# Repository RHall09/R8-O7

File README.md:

R8-O7

A repository containing source code for running an autonomous crowd interaction robot.

See https://rhall09.github.io/R8-O7/html/index.html#sec_intro for documentation and inspirations.

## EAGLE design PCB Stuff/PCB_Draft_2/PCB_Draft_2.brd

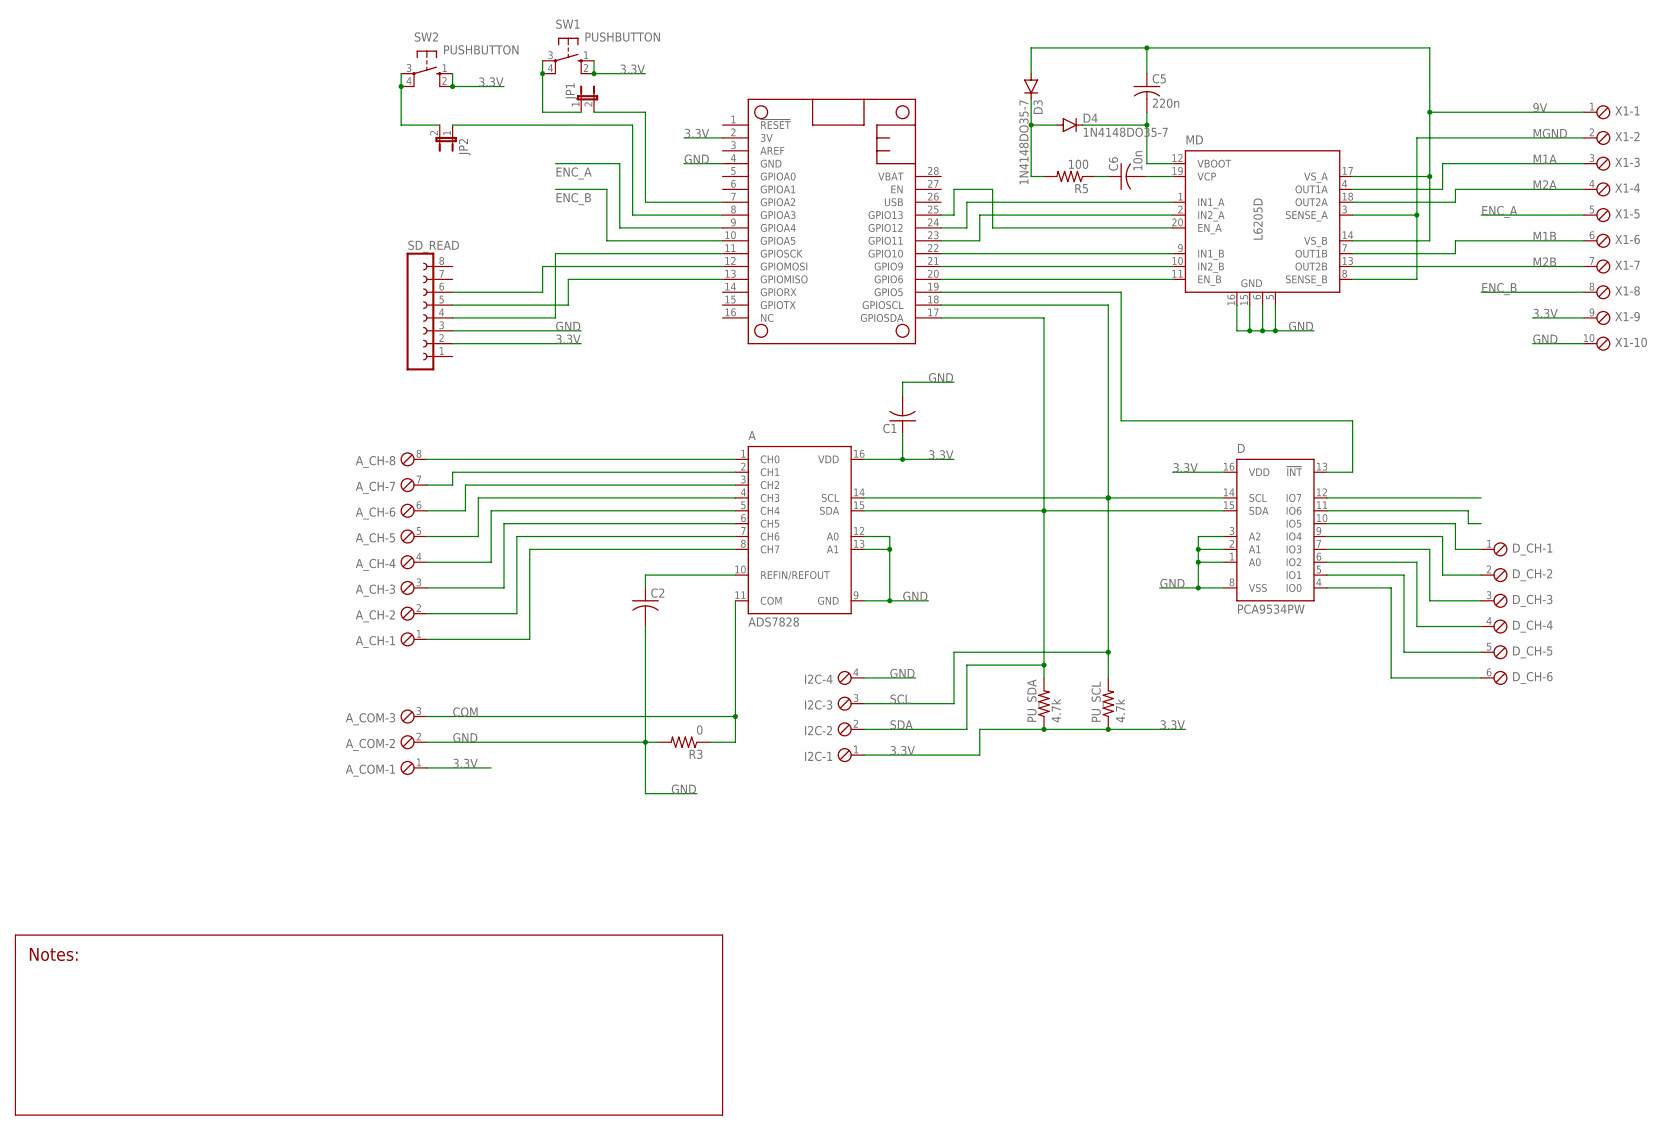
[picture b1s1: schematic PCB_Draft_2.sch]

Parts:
A: ADS7828; TSSOP16-PW
A_CH: SCREWTERM_8P_254; 8POL254
A_COM: SCREWTERM_3P_254; 3POL254
C1, C2: C-USC0805; C0805
C5: 220n; C0805
C6: 10n; C0805
D: PCA9534PW; TSSOP16
D3, D4: 1N4148DO35-7; DO35-7
D_CH: SCREWTERM_6P_254; 6POL254
FTHRWNG: FEATHERWINGEXTENDED_BOTH_ENDS; FEATHERWING
I2C: SCREWTERM_4P_254; 4POL254
JP1, JP2: JP1E; JP1
MD: L6205D; SO20
PU_SCL: 4.7k; M0805
PU_SDA: 4.7k; M0805
R3: 0; M0805
R5: 100; M0805
SD_READ: FE08-1; FE08
SW1, SW2: PUSHBUTTON; B3F-10XX
X1: SCREWTERM_10P_254; 10POL254

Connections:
3.3V: A.16 (VDD), A_COM.1, C1.1, D.16 (VDD), FTHRWNG.2 (3V), I2C.1, PU_SCL.1, PU_SDA.1, SD_READ.2, SW1.1 (S), SW1.2 (S1), SW2.1 (S), SW2.2 (S1), X1.9
9V: C5.1, D3.A, MD.14 (VS_B), MD.17 (VS_A), X1.1
COM: A.11 (COM), A_COM.3, R3.1
ENC_A: FTHRWNG.9 (GPIOA4), X1.5
ENC_B: FTHRWNG.10 (GPIOA5), X1.8
GND: A.9 (GND), A.12 (A0), A.13 (A1), A_COM.2, C1.2, C2.2, D.1 (A0), D.2 (A1), D.3 (A2), D.8 (VSS), FTHRWNG.4 (GND), I2C.4, MD.5 (GND), MD.6 (GND), MD.15 (GND), MD.16 (GND), R3.2, SD_READ.3, X1.10
M1A: MD.4 (OUT1A), X1.3
M1B: MD.7 (OUT1B), X1.6
M2A: MD.18 (OUT2A), X1.4
M2B: MD.13 (OUT2B), X1.7
MGND: MD.3 (SENSE_A), MD.8 (SENSE_B), X1.2
unnamed: D.10 (IO5), D_CH.1
unnamed: D.9 (IO4), D_CH.2
unnamed: D.7 (IO3), D_CH.3
unnamed: D.6 (IO2), D_CH.4
unnamed: D.5 (IO1), D_CH.5
unnamed: D.4 (IO0), D_CH.6
unnamed: A.1 (CH0), A_CH.8
unnamed: A.2 (CH1), A_CH.7
unnamed: A.3 (CH2), A_CH.6
unnamed: A.4 (CH3), A_CH.5
unnamed: A.5 (CH4), A_CH.4
unnamed: A.6 (CH5), A_CH.3
unnamed: A.7 (CH6), A_CH.2
unnamed: A.8 (CH7), A_CH.1
unnamed: A.10 (REFIN/REFOUT), C2.1
unnamed: FTHRWNG.20 (GPIO6), MD.11 (EN_B)
unnamed: D.13 (!INT), FTHRWNG.19 (GPIO5)
unnamed: FTHRWNG.21 (GPIO9), MD.10 (IN2_B)
unnamed: FTHRWNG.22 (GPIO10), MD.9 (IN1_B)
unnamed: FTHRWNG.23 (GPIO11), MD.2 (IN2_A)
unnamed: FTHRWNG.24 (GPIO12), MD.1 (IN1_A)
unnamed: FTHRWNG.11 (GPIOSCK), SD_READ.4
unnamed: FTHRWNG.25 (GPIO13), MD.20 (EN_A)
unnamed: JP1.1, SW1.3, SW1.4 (P1)
unnamed: JP2.2, SW2.3, SW2.4 (P1)
unnamed: FTHRWNG.13 (GPIOMISO), SD_READ.5
unnamed: FTHRWNG.8 (GPIOA3), JP2.1
unnamed: FTHRWNG.7 (GPIOA2), JP1.2
unnamed: FTHRWNG.12 (GPIOMOSI), SD_READ.6
unnamed: C6.2, MD.19 (VCP)
unnamed: C6.1, R5.1
unnamed: D3.C, D4.A, R5.2
unnamed: C5.2, D4.C, MD.12 (VBOOT)
SCL: A.14 (SCL), D.14 (SCL), FTHRWNG.18 (GPIOSCL), I2C.3, PU_SCL.2
SDA: A.15 (SDA), D.15 (SDA), FTHRWNG.17 (GPIOSDA), I2C.2, PU_SDA.2

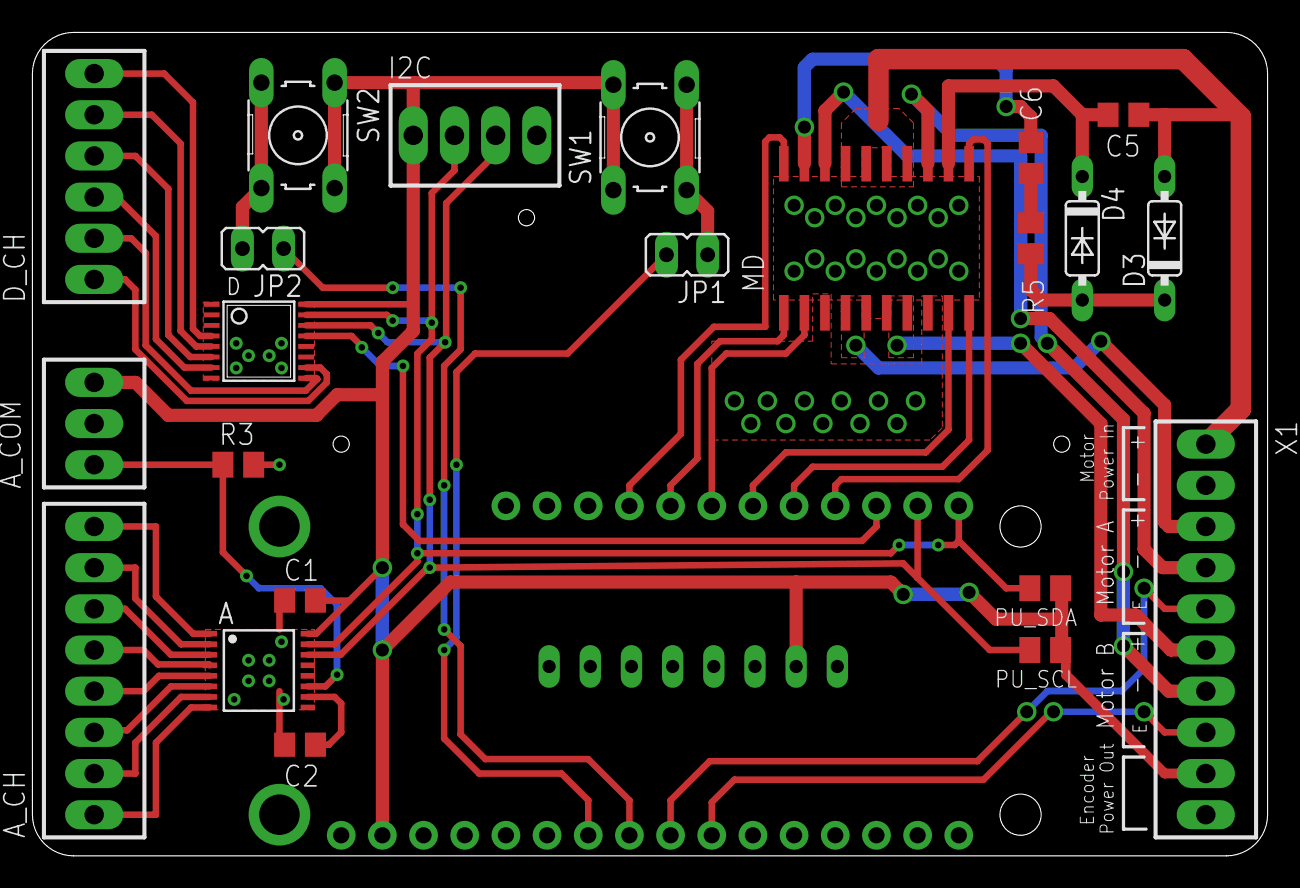
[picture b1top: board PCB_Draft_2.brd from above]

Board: 2 copper layers, 76.2 x 50.8 mm, 24 parts (1 on the bottom side), 46 nets.

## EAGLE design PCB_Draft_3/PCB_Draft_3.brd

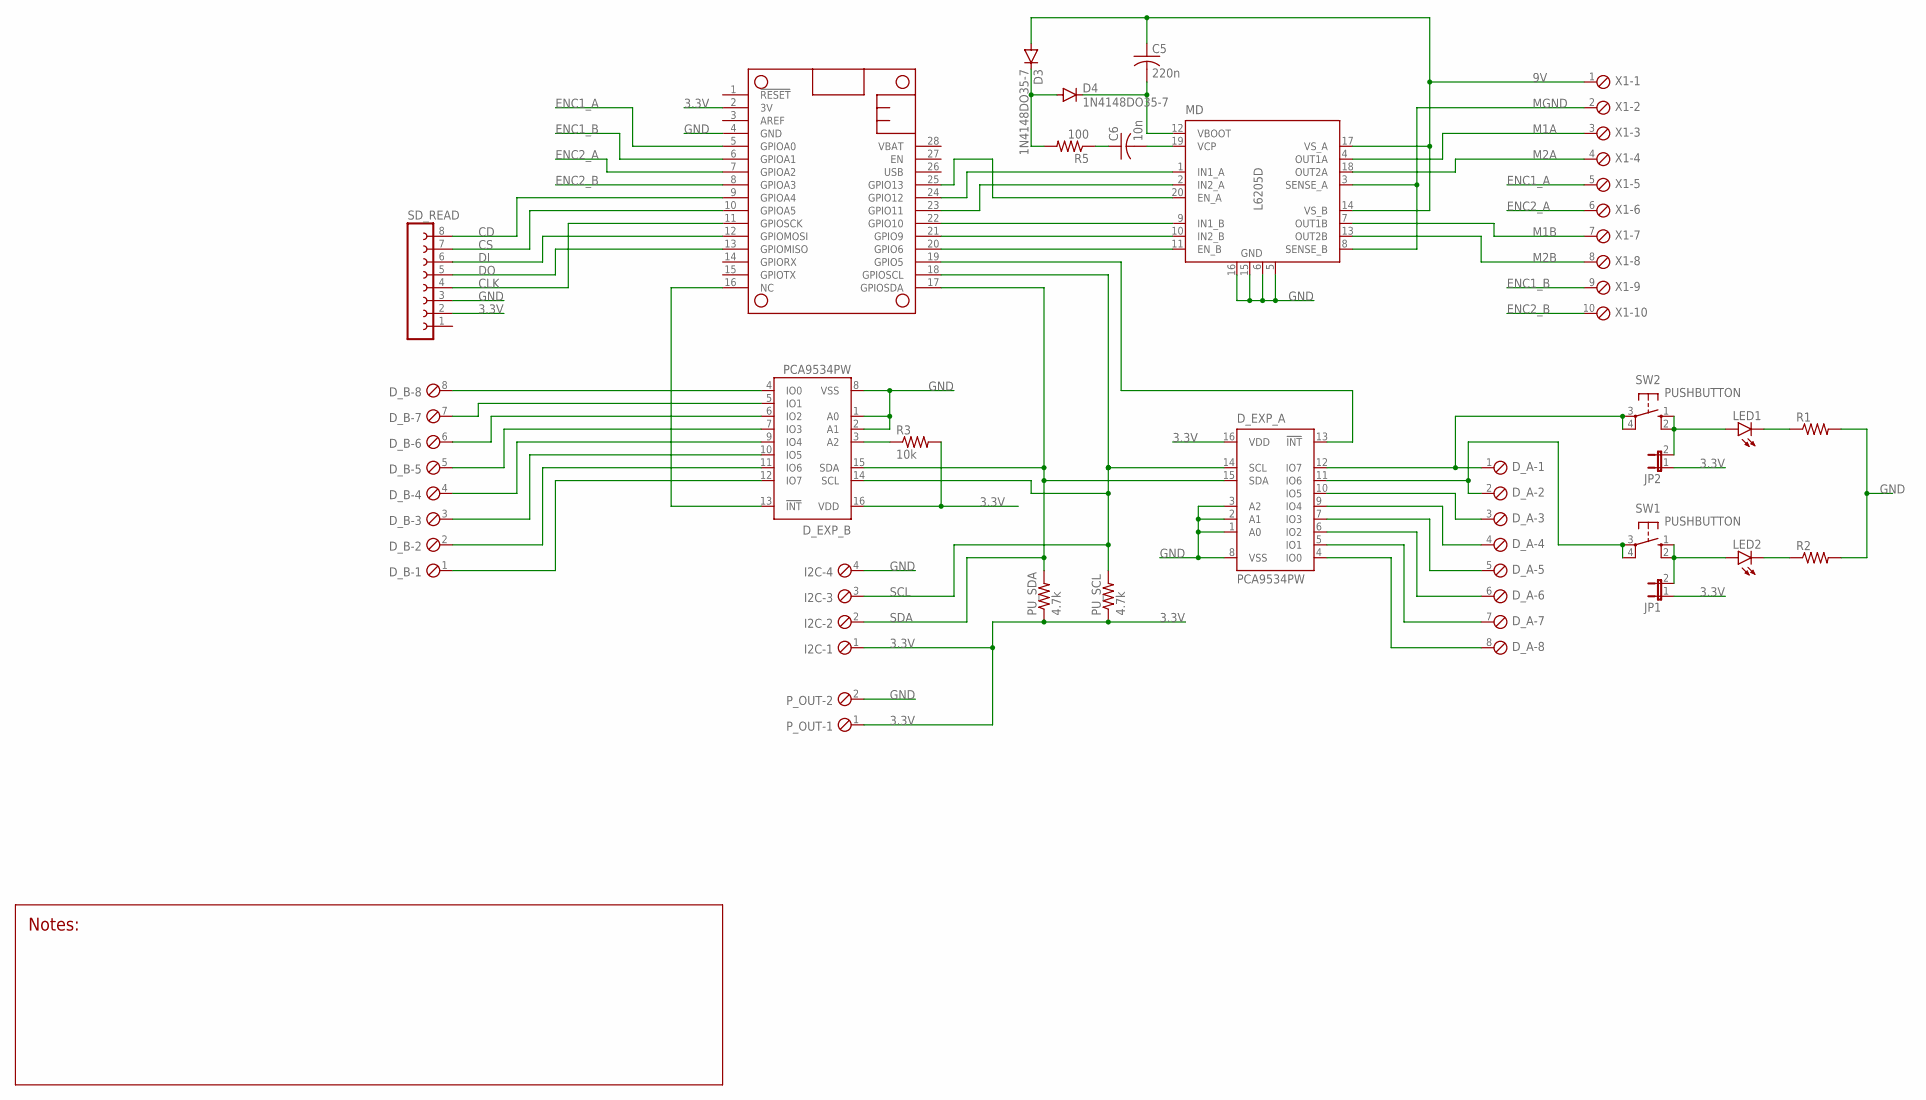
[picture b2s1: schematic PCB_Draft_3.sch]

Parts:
C5: 220n; C0805
C6: 10n; C0805
D3, D4: 1N4148DO35-7; DO35-7
D_A: SCREWTERM_8P_254; 8POL254
D_B: SCREWTERM_8P_254; 8POL254
D_EXP_A: PCA9534PW; TSSOP16
D_EXP_B: PCA9534PW; TSSOP16
FTHRWNG: FEATHERWINGEXTENDED_BOTH_ENDS; FEATHERWING
I2C: SCREWTERM_4P_254; 4POL254
JP1, JP2: JP1E; JP1
LED1, LED2: LEDCHIPLED_0805; CHIPLED_0805
MD: L6205D; SO20
PU_SCL: 4.7k; M0805
PU_SDA: 4.7k; M0805
P_OUT: SCREWTERM_2P_254; 2POL254
R1, R2: R-US_M0805; M0805
R3: 10k; M0805
R5: 100; M0805
SD_READ: FE08-1; FE08
SW1, SW2: PUSHBUTTON; B3F-10XX
X1: SCREWTERM_10P_254; 10POL254

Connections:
3.3V: D_EXP_A.16 (VDD), D_EXP_B.16 (VDD), FTHRWNG.2 (3V), I2C.1, JP1.1, JP2.1, PU_SCL.1, PU_SDA.1, P_OUT.1, R3.2, SD_READ.2
9V: C5.1, D3.A, MD.14 (VS_B), MD.17 (VS_A), X1.1
CD: FTHRWNG.9 (GPIOA4), SD_READ.8
CLK: FTHRWNG.11 (GPIOSCK), SD_READ.4
CS: FTHRWNG.10 (GPIOA5), SD_READ.7
DI: FTHRWNG.12 (GPIOMOSI), SD_READ.6
DO: FTHRWNG.13 (GPIOMISO), SD_READ.5
ENC1_A: FTHRWNG.5 (GPIOA0), X1.5
ENC1_B: FTHRWNG.6 (GPIOA1), X1.9
ENC2_A: FTHRWNG.7 (GPIOA2), X1.6
ENC2_B: FTHRWNG.8 (GPIOA3), X1.10
GND: D_EXP_A.1 (A0), D_EXP_A.2 (A1), D_EXP_A.3 (A2), D_EXP_A.8 (VSS), D_EXP_B.1 (A0), D_EXP_B.2 (A1), D_EXP_B.8 (VSS), FTHRWNG.4 (GND), I2C.4, MD.5 (GND), MD.6 (GND), MD.15 (GND), MD.16 (GND), P_OUT.2, R1.2, R2.2, SD_READ.3
M1A: MD.4 (OUT1A), X1.3
M1B: MD.7 (OUT1B), X1.7
M2A: MD.18 (OUT2A), X1.4
M2B: MD.13 (OUT2B), X1.8
MGND: MD.3 (SENSE_A), MD.8 (SENSE_B), X1.2
unnamed: D_A.1, D_EXP_A.12 (IO7), SW2.3, SW2.4 (P1)
unnamed: D_A.2, D_EXP_A.11 (IO6), SW1.3, SW1.4 (P1)
unnamed: D_A.3, D_EXP_A.10 (IO5)
unnamed: D_A.4, D_EXP_A.9 (IO4)
unnamed: D_A.5, D_EXP_A.7 (IO3)
unnamed: D_A.6, D_EXP_A.6 (IO2)
unnamed: D_A.7, D_EXP_A.5 (IO1)
unnamed: D_A.8, D_EXP_A.4 (IO0)
unnamed: D_B.8, D_EXP_B.4 (IO0)
unnamed: D_B.7, D_EXP_B.5 (IO1)
unnamed: D_B.6, D_EXP_B.6 (IO2)
unnamed: D_B.5, D_EXP_B.7 (IO3)
unnamed: D_B.4, D_EXP_B.9 (IO4)
unnamed: D_B.3, D_EXP_B.10 (IO5)
unnamed: D_B.2, D_EXP_B.11 (IO6)
unnamed: D_B.1, D_EXP_B.12 (IO7)
unnamed: LED2.C, R2.1
unnamed: FTHRWNG.20 (GPIO6), MD.11 (EN_B)
unnamed: D_EXP_A.13 (!INT), FTHRWNG.19 (GPIO5)
unnamed: FTHRWNG.21 (GPIO9), MD.10 (IN2_B)
unnamed: FTHRWNG.22 (GPIO10), MD.9 (IN1_B)
unnamed: FTHRWNG.23 (GPIO11), MD.2 (IN2_A)
unnamed: FTHRWNG.24 (GPIO12), MD.1 (IN1_A)
unnamed: JP2.2, LED1.A, SW2.1 (S), SW2.2 (S1)
unnamed: FTHRWNG.25 (GPIO13), MD.20 (EN_A)
unnamed: JP1.2, LED2.A, SW1.1 (S), SW1.2 (S1)
unnamed: D_EXP_B.13 (!INT), FTHRWNG.16 (NC)
unnamed: LED1.C, R1.1
unnamed: D_EXP_B.3 (A2), R3.1
unnamed: C6.2, MD.19 (VCP)
unnamed: C6.1, R5.1
unnamed: D3.C, D4.A, R5.2
unnamed: C5.2, D4.C, MD.12 (VBOOT)
SCL: D_EXP_A.14 (SCL), D_EXP_B.14 (SCL), FTHRWNG.18 (GPIOSCL), I2C.3, PU_SCL.2
SDA: D_EXP_A.15 (SDA), D_EXP_B.15 (SDA), FTHRWNG.17 (GPIOSDA), I2C.2, PU_SDA.2

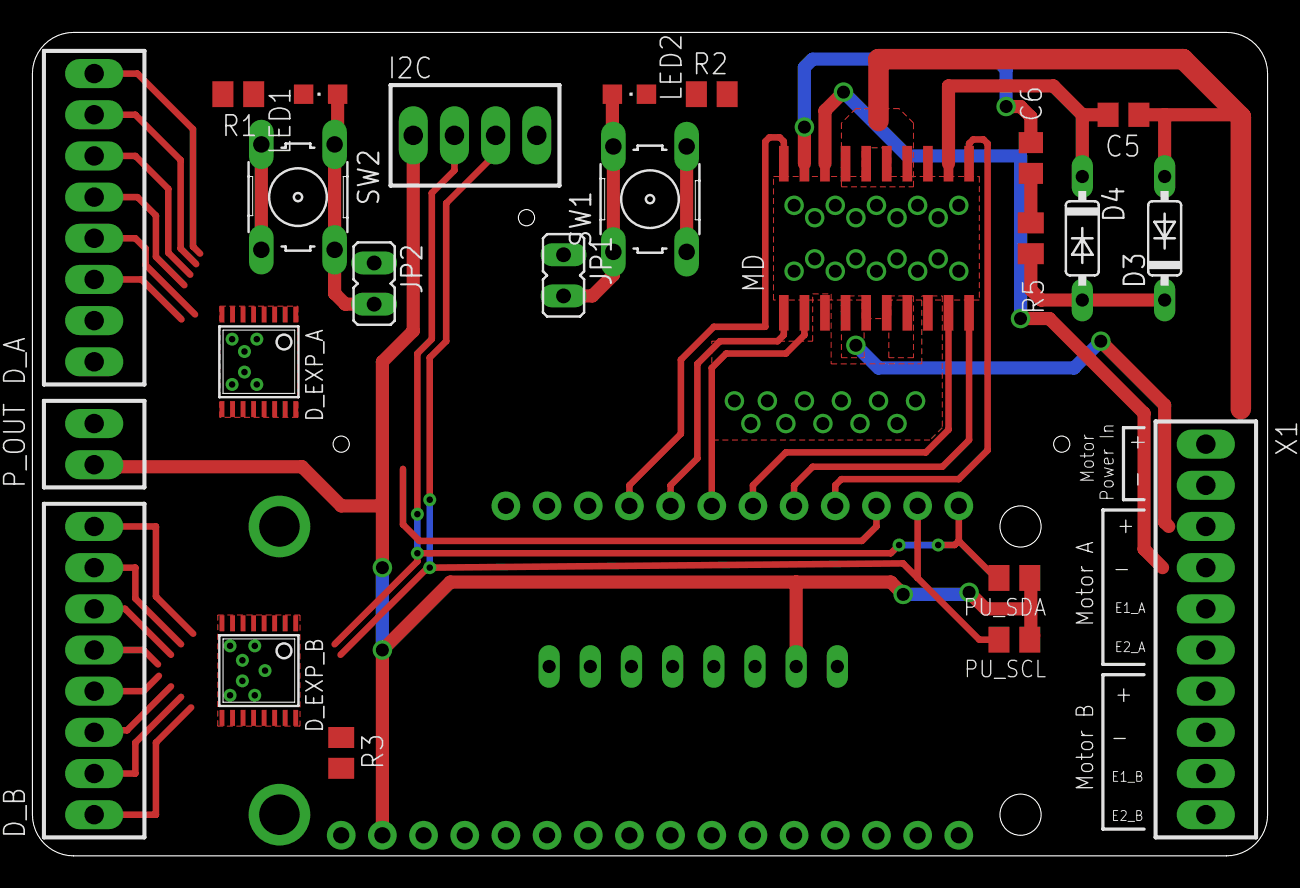
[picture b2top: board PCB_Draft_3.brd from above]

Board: 2 copper layers, 76.2 x 50.8 mm, 26 parts (1 on the bottom side), 52 nets.

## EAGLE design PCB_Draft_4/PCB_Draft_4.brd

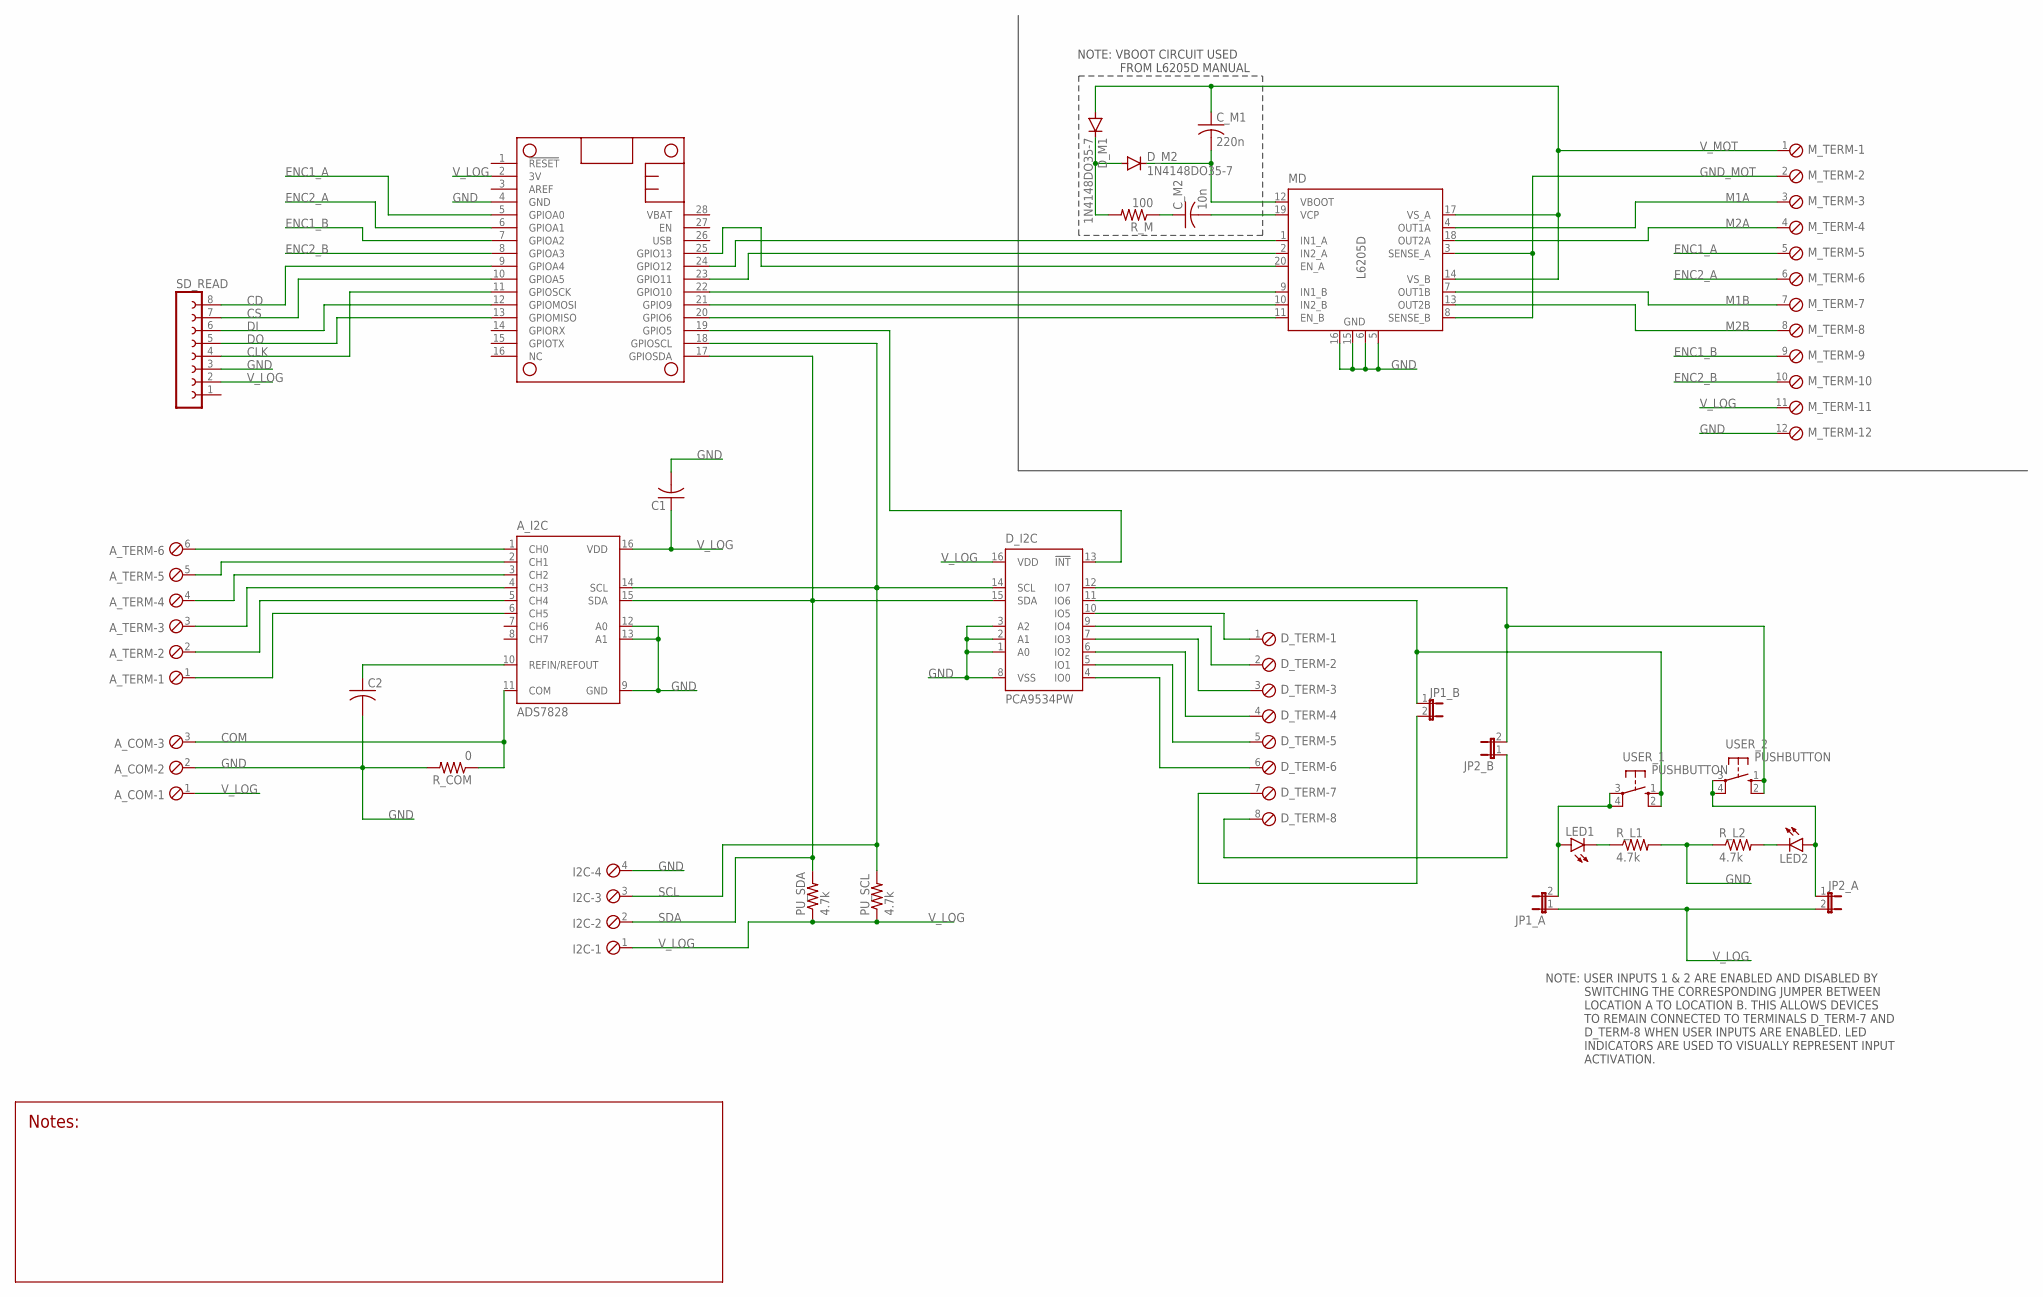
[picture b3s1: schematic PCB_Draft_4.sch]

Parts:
A_COM: SCREWTERM_3P_254; 3POL254
A_I2C: ADS7828; TSSOP16-PW
A_TERM: SCREWTERM_6P_254; 6POL254
C1, C2: C-USC0805; C0805
C_M1: 220n; C0805
C_M2: 10n; C0805
D_I2C: PCA9534PW; TSSOP16
D_M1, D_M2: 1N4148DO35-7; DO35-7
D_TERM: SCREWTERM_8P_254; 8POL254
FTHRWNG: FEATHERWINGEXTENDED_BOTH_ENDS; FEATHERWING
I2C: SCREWTERM_4P_254; 4POL254
JP1_A, JP1_B, JP2_A, JP2_B: JP1E; JP1
LED1, LED2: LEDCHIP-LED0805; CHIP-LED0805
MD: L6205D; SO20
M_TERM: SCREWTERM_12P_254; 12POL254
PU_SCL: 4.7k; M0805
PU_SDA: 4.7k; M0805
R_COM: 0; M0805
R_L1, R_L2: 4.7k; M0805
R_M: 100; M0805
SD_READ: FE08-1; FE08
USER_1, USER_2: PUSHBUTTON; B3F-10XX

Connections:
CD: FTHRWNG.9 (GPIOA4), SD_READ.8
CLK: FTHRWNG.11 (GPIOSCK), SD_READ.4
COM: A_COM.3, A_I2C.11 (COM), R_COM.1
CS: FTHRWNG.10 (GPIOA5), SD_READ.7
DI: FTHRWNG.12 (GPIOMOSI), SD_READ.6
DO: FTHRWNG.13 (GPIOMISO), SD_READ.5
ENC1_A: FTHRWNG.5 (GPIOA0), M_TERM.5
ENC1_B: FTHRWNG.7 (GPIOA2), M_TERM.9
ENC2_A: FTHRWNG.6 (GPIOA1), M_TERM.6
ENC2_B: FTHRWNG.8 (GPIOA3), M_TERM.10
GND: A_COM.2, A_I2C.9 (GND), A_I2C.12 (A0), A_I2C.13 (A1), C1.2, C2.2, D_I2C.1 (A0), D_I2C.2 (A1), D_I2C.3 (A2), D_I2C.8 (VSS), FTHRWNG.4 (GND), I2C.4, MD.5 (GND), MD.6 (GND), MD.15 (GND), MD.16 (GND), M_TERM.12, R_COM.2, R_L1.2, R_L2.1, SD_READ.3
GND_MOT: MD.3 (SENSE_A), MD.8 (SENSE_B), M_TERM.2
M1A: MD.4 (OUT1A), M_TERM.3
M1B: MD.7 (OUT1B), M_TERM.7
M2A: MD.18 (OUT2A), M_TERM.4
M2B: MD.13 (OUT2B), M_TERM.8
unnamed: D_I2C.12 (IO7), JP2_B.2, USER_2.1 (S), USER_2.2 (S1)
unnamed: D_I2C.11 (IO6), JP1_B.1, USER_1.1 (S), USER_1.2 (S1)
unnamed: D_I2C.10 (IO5), D_TERM.1
unnamed: D_I2C.9 (IO4), D_TERM.2
unnamed: D_I2C.7 (IO3), D_TERM.3
unnamed: D_I2C.6 (IO2), D_TERM.4
unnamed: D_TERM.7, JP1_B.2
unnamed: A_I2C.1 (CH0), A_TERM.6
unnamed: A_I2C.2 (CH1), A_TERM.5
unnamed: A_I2C.3 (CH2), A_TERM.4
unnamed: A_I2C.4 (CH3), A_TERM.3
unnamed: A_I2C.5 (CH4), A_TERM.2
unnamed: A_I2C.6 (CH5), A_TERM.1
unnamed: A_I2C.10 (REFIN/REFOUT), C2.1
unnamed: FTHRWNG.20 (GPIO6), MD.11 (EN_B)
unnamed: D_I2C.13 (!INT), FTHRWNG.19 (GPIO5)
unnamed: FTHRWNG.21 (GPIO9), MD.10 (IN2_B)
unnamed: FTHRWNG.22 (GPIO10), MD.9 (IN1_B)
unnamed: FTHRWNG.23 (GPIO11), MD.2 (IN2_A)
unnamed: FTHRWNG.24 (GPIO12), MD.1 (IN1_A)
unnamed: FTHRWNG.25 (GPIO13), MD.20 (EN_A)
unnamed: JP1_A.2, LED1.A, USER_1.3, USER_1.4 (P1)
unnamed: JP2_A.1, LED2.A, USER_2.3, USER_2.4 (P1)
unnamed: LED1.C, R_L1.1
unnamed: LED2.C, R_L2.2
unnamed: D_I2C.5 (IO1), D_TERM.5
unnamed: D_I2C.4 (IO0), D_TERM.6
unnamed: D_TERM.8, JP2_B.1
unnamed: C_M2.1, R_M.1
unnamed: D_M1.C, D_M2.A, R_M.2
SCL: A_I2C.14 (SCL), D_I2C.14 (SCL), FTHRWNG.18 (GPIOSCL), I2C.3, PU_SCL.2
SDA: A_I2C.15 (SDA), D_I2C.15 (SDA), FTHRWNG.17 (GPIOSDA), I2C.2, PU_SDA.2
VBOOT: C_M1.2, D_M2.C, MD.12 (VBOOT)
VCP: C_M2.2, MD.19 (VCP)
V_LOG: A_COM.1, A_I2C.16 (VDD), C1.1, D_I2C.16 (VDD), FTHRWNG.2 (3V), I2C.1, JP1_A.1, JP2_A.2, M_TERM.11, PU_SCL.1, PU_SDA.1, SD_READ.2
V_MOT: C_M1.1, D_M1.A, MD.14 (VS_B), MD.17 (VS_A), M_TERM.1

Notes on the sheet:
NOTE: VBOOT CIRCUIT USED FROM L6205D MANUAL
NOTE: USER INPUTS 1 & 2 ARE ENABLED AND DISABLED BY SWITCHING THE CORRESPONDING JUMPER BETWEEN LOCATION A TO LOCATION B. THIS ALLOWS DEVICES TO REMAIN CONNECTED TO TERMINALS D_TERM-7 AND D_TERM-8 WHEN USER INPUTS ARE ENABLED. LED INDICATORS ARE USED TO VISUALLY REPRESENT INPUT ACTIVATION.

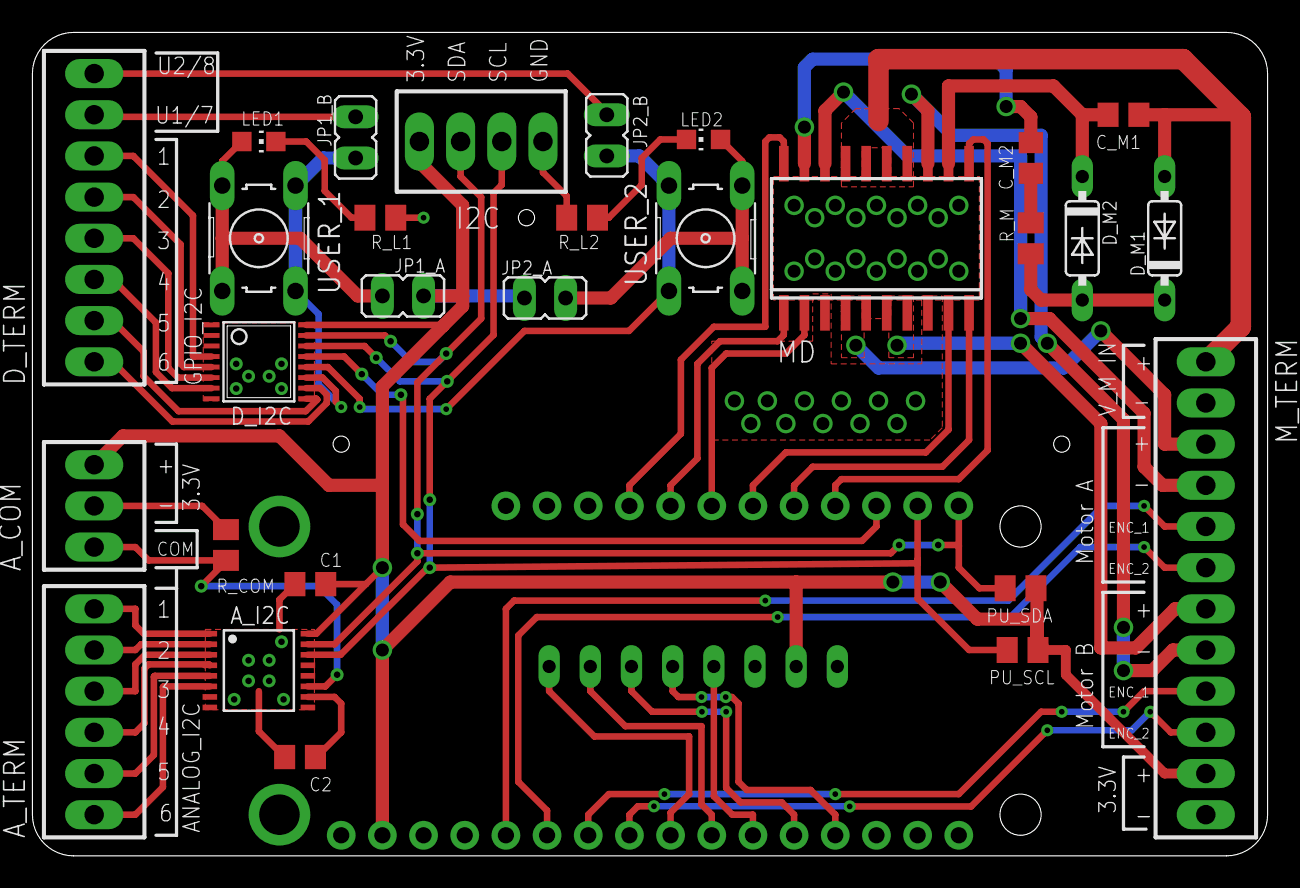
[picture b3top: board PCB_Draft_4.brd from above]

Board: 2 copper layers, 76.2 x 50.8 mm, 30 parts (1 on the bottom side), 52 nets.

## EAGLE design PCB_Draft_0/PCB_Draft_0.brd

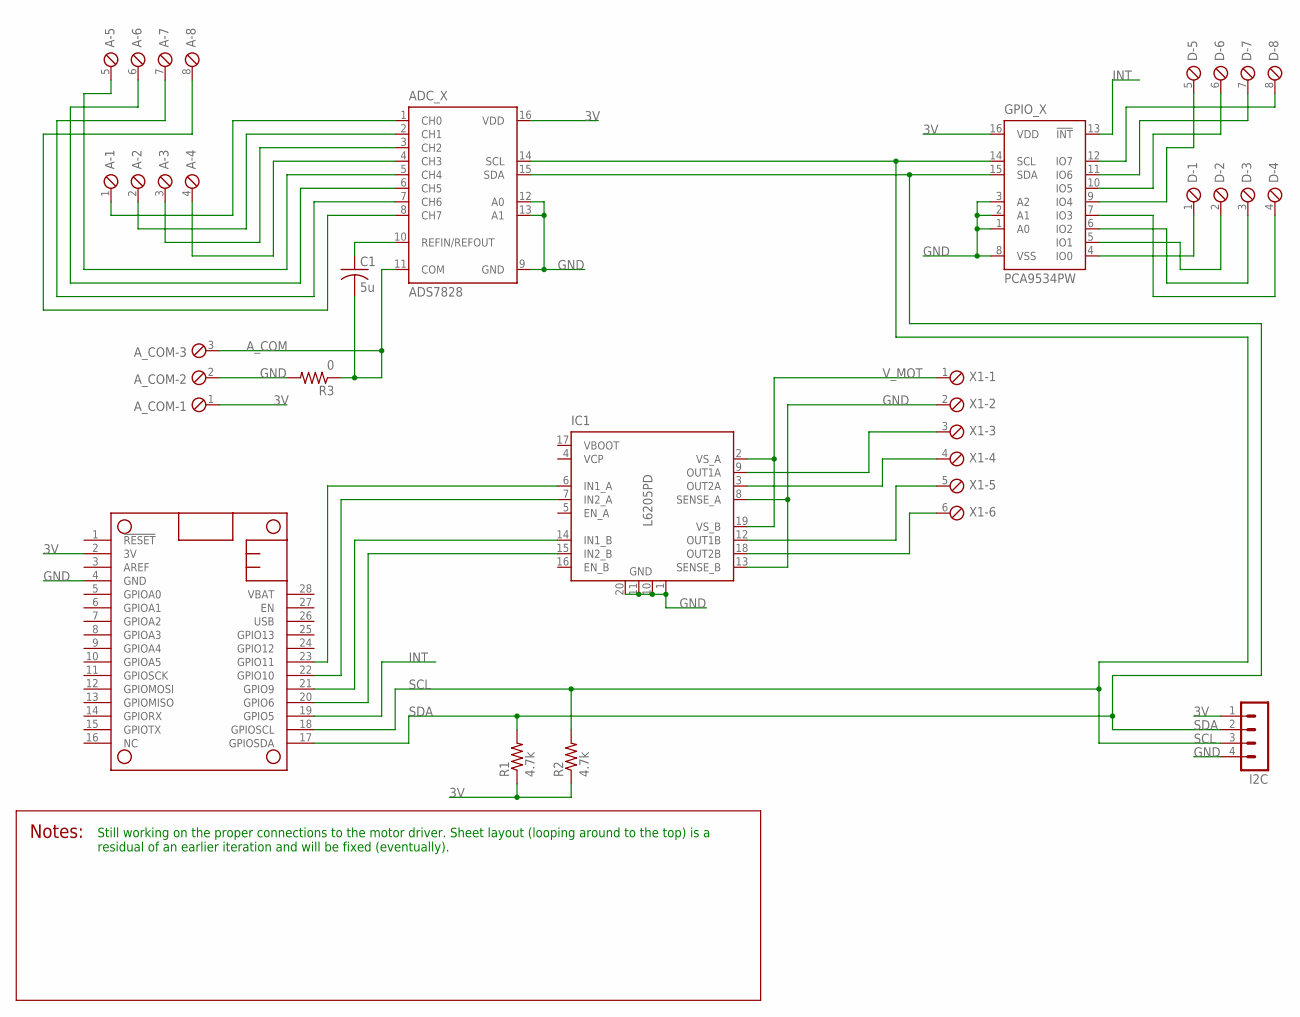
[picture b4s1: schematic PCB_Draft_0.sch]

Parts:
A: SCREWTERM_8P_254; 8POL254
ADC_X: ADS7828; TSSOP16-PW
A_COM: SCREWTERM_3P_254; 3POL254
C1: 5u; C0805
D: SCREWTERM_8P_254; 8POL254
GPIO_X: PCA9534PW; TSSOP16
I2C: MA04-1
IC1: L6205PD; POWERSO-20
MS1: FEATHERWINGEXTENDED_BOTH_ENDS; FEATHERWING
R1, R2: 4.7k; R0805
R3: 0; M0805
X1: SCREWTERM_6P_254; 6POL254

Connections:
3V: ADC_X.16 (VDD), A_COM.1, GPIO_X.16 (VDD), I2C.1, MS1.2 (3V), R1.1, R2.1
A_COM: ADC_X.11 (COM), A_COM.3, C1.2, R3.1
GND: ADC_X.9 (GND), ADC_X.12 (A0), ADC_X.13 (A1), A_COM.2, GPIO_X.1 (A0), GPIO_X.2 (A1), GPIO_X.3 (A2), GPIO_X.8 (VSS), I2C.4, IC1.1 (GND), IC1.8 (SENSE_A), IC1.10 (GND), IC1.11 (GND), IC1.13 (SENSE_B), IC1.20 (GND), MS1.4 (GND), R3.2, X1.2
INT: GPIO_X.13 (!INT), MS1.19 (GPIO5)
unnamed: D.1, GPIO_X.4 (IO0)
unnamed: D.2, GPIO_X.5 (IO1)
unnamed: D.3, GPIO_X.6 (IO2)
unnamed: D.4, GPIO_X.7 (IO3)
unnamed: D.5, GPIO_X.9 (IO4)
unnamed: D.6, GPIO_X.10 (IO5)
unnamed: D.7, GPIO_X.11 (IO6)
unnamed: D.8, GPIO_X.12 (IO7)
unnamed: A.1, ADC_X.1 (CH0)
unnamed: A.2, ADC_X.2 (CH1)
unnamed: A.3, ADC_X.3 (CH2)
unnamed: A.4, ADC_X.4 (CH3)
unnamed: A.5, ADC_X.5 (CH4)
unnamed: A.6, ADC_X.6 (CH5)
unnamed: A.7, ADC_X.7 (CH6)
unnamed: A.8, ADC_X.8 (CH7)
unnamed: ADC_X.10 (REFIN/REFOUT), C1.1
unnamed: IC1.9 (OUT1A), X1.3
unnamed: IC1.3 (OUT2A), X1.4
unnamed: IC1.12 (OUT1B), X1.5
unnamed: IC1.18 (OUT2B), X1.6
unnamed: IC1.6 (IN1_A), MS1.23 (GPIO11)
unnamed: IC1.15 (IN2_B), MS1.20 (GPIO6)
unnamed: IC1.14 (IN1_B), MS1.21 (GPIO9)
unnamed: IC1.7 (IN2_A), MS1.22 (GPIO10)
SCL: ADC_X.14 (SCL), GPIO_X.14 (SCL), I2C.3, MS1.18 (GPIOSCL), R2.2
SDA: ADC_X.15 (SDA), GPIO_X.15 (SDA), I2C.2, MS1.17 (GPIOSDA), R1.2
VBOOT: IC1.17 (VBOOT)
VCP: IC1.4 (VCP)
V_MOT: IC1.2 (VS_A), IC1.19 (VS_B), X1.1

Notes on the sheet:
Still working on the proper connections to the motor driver. Sheet layout (looping around to the top) is a residual of an earlier iteration and will be fixed (eventually).

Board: 2 copper layers, 13 parts (0 on the bottom side), 32 nets, no tracks yet.

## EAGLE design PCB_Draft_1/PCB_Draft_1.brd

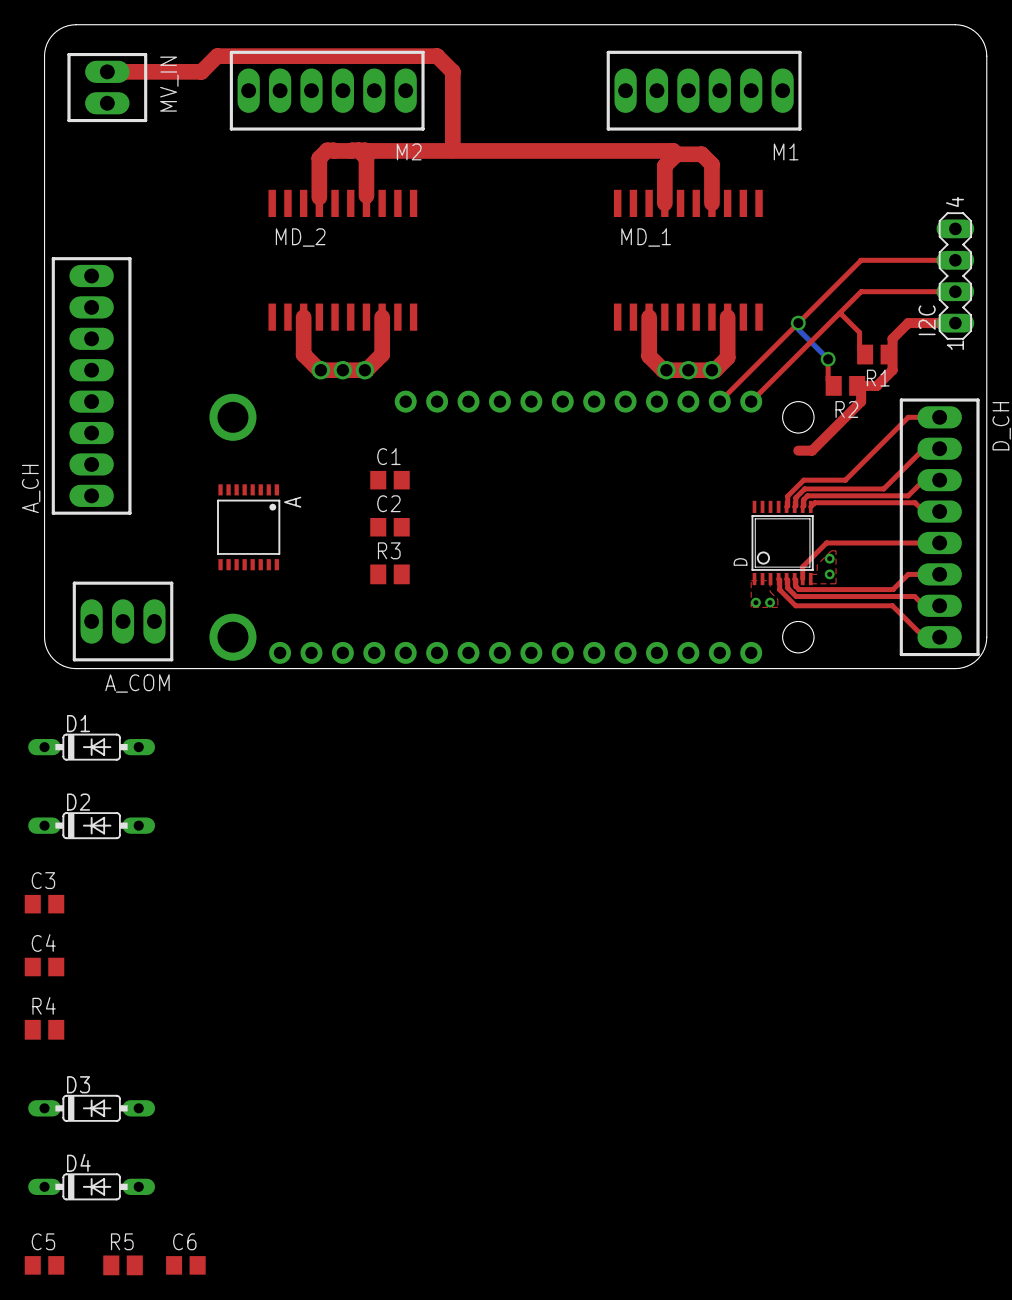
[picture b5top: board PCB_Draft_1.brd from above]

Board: 2 copper layers, 76.2 x 52.1 mm, 27 parts (0 on the bottom side), 53 nets.

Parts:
A: ADS7828; TSSOP16-PW
A_CH: 8POL254
A_COM: 3POL254
C1, C2: C0805
C3, C5: 220n; C0805
C4, C6: 10n; C0805
D: PCA9534PW; TSSOP16
D1, D2, D3, D4: 1N4148DO35-7; DO35-7
D_CH: 8POL254
FTHRWNG: FEATHERWINGEXTENDED_BOTH_ENDS; FEATHERWING
I2C: MA04-1
M1, M2: 6POL254
MD_1, MD_2: L6205D; SO20
MV_IN: 2POL254
R1, R2: 4.7k; M0805
R3: 0; M0805
R4, R5: 100; M0805

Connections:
3.3V: A.16, A_COM.1, C1.1, D.16, FTHRWNG.2, I2C.1, R1.1, R2.1
9V: C3.1, C5.1, D1.A, D3.A, MD_1.14, MD_1.17, MD_2.14, MD_2.17, MV_IN.1
COM: A.11, A_COM.3, R3.1
GND: A.9, A.12, A.13, A_COM.2, C1.2, C2.2, D.1, D.2, D.3, D.8, FTHRWNG.4, I2C.4, MD_1.5, MD_1.6, MD_1.15, MD_1.16, MD_2.5, MD_2.6, MD_2.15, MD_2.16, R3.2
MGND: MD_1.3, MD_1.8, MD_2.3, MD_2.8, MV_IN.2
unnamed: D.12, D_CH.1
unnamed: D.11, D_CH.2
unnamed: D.10, D_CH.3
unnamed: D.9, D_CH.4
unnamed: D.7, D_CH.5
unnamed: D.6, D_CH.6
unnamed: D.5, D_CH.7
unnamed: D.4, D_CH.8
unnamed: A.1, A_CH.8
unnamed: A.2, A_CH.7
unnamed: A.3, A_CH.6
unnamed: A.4, A_CH.5
unnamed: A.5, A_CH.4
unnamed: A.6, A_CH.3
unnamed: A.7, A_CH.2
unnamed: A.8, A_CH.1
unnamed: A.10, C2.1
unnamed: C4.2, MD_1.19
unnamed: D.13, FTHRWNG.19
unnamed: M1.1, MD_1.4
unnamed: M1.2, MD_1.7
unnamed: M1.4, MD_1.18
unnamed: M1.5, MD_1.13
unnamed: M2.1, MD_2.4
unnamed: C4.1, R4.1
unnamed: M2.2, MD_2.7
unnamed: M2.4, MD_2.18
unnamed: M2.5, MD_2.13
unnamed: FTHRWNG.20, MD_2.10
unnamed: FTHRWNG.22, MD_2.9
unnamed: FTHRWNG.21, MD_2.2
unnamed: FTHRWNG.23, MD_2.1
unnamed: FTHRWNG.10, MD_1.1
unnamed: FTHRWNG.8, MD_1.2
unnamed: FTHRWNG.9, MD_1.9
unnamed: FTHRWNG.7, MD_1.10
unnamed: FTHRWNG.24, MD_2.11
unnamed: FTHRWNG.25, MD_2.20
unnamed: FTHRWNG.6, MD_1.20
unnamed: FTHRWNG.5, MD_1.11
unnamed: D1.C, D2.A, R4.2
unnamed: C3.2, D2.C, MD_1.12
unnamed: C6.2, MD_2.19
unnamed: C6.1, R5.1
unnamed: D3.C, D4.A, R5.2
unnamed: C5.2, D4.C, MD_2.12
SCL: A.14, D.14, FTHRWNG.18, I2C.3, R2.2
SDA: A.15, D.15, FTHRWNG.17, I2C.2, R1.2

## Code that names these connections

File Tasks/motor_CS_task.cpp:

/** @file motor_CS_task.cpp
 *  This file contains a task which... 
 * 
 *  @author Rick Hall
 *  @date   2021-Nov-27 Original file
 */

#include <Arduino.h>
#if (defined STM32L4xx || defined STM32F4xx)
    #include <STM32FreeRTOS.h>
#endif

#include "shares.h"                          // Header for shares used in this project
#include "MotorCS.h"
#include "Motor.h"

#define EVER (;;)

void motor_task (void* p_params) 
{
    
    Motor motorA(GPIO13,GPIO12,GPIO11);     // Set up Left Motor
    MotorCS motAc(void);
    motorA.enable();
    Motor motorB(GPIO6,GPIO9,GPIO10);       // Set up Right Motor
    MotorCS motBc(void);
    motorB.enable();



    for EVER 
    {
        // Get motor flag register from share
        current_flag = motorFlagRegister.get();

        // Check motors for overcurrent fault
        motorA.checkOvercurrent();
        motorB.checkOvercurrent();

        if(!(motorA.FlagChk(ERROR) && motorB.FlagChk(ERROR)))
        {

            // Grab the last encoder velocity value and delta time, then run the
            if()
            { 
                encA_vel = encoderA_velocity_queue.get();
                encB_vel = encoderB_velocity_queue.get();
                encA_dt  = encoderA_dtime_queue.get();
                encB_dt  = encoderB_dtime_queue.get();
                
                // Get new setpoints and load into CS, if necessary
                if()
                {
                    motAc.newSetpoint(motorA_Set.get());
                }
                if()
                {
                    motBc.newSetpoint(motorB_Set.get());
                }        

                // Run control systems (toggle each time to average out computational difference in time between motors)
                static bool tog = true;     // boolean to average out minor variations in motor opearation
                if(tog)
                {
                    motAc.run(motorA,encA_vel,encA_dt);
                    motBC.run(motorB,encB_vel,encB_dt);
                }
                else
                {
                    motBc.run(motorB,encB_vel,encB_dt);
                    motAC.run(motorA,encA_vel,encA_dt);
                }
                tog = !tog;    
            }  
            
        }
        else
        {
            // When clear overcurrent flag is raised, clear motors to run again.
            if()
            {
                motorA.clearOvercurrent()
                motorB.clearOvercurrent()
            }
        }

    }

    // vTaskDelay(5)    Currently delays for 5 seconds

}
